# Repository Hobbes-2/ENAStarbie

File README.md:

ENA Themed Starbie

This project builds off of the basic Starbie tutorial with a focus on the game ENA: Dream BBQ. (In case you cant tell, ive been playing it). This is for week 1 of Hackclub Half Life. 

Its a fairly simple tamogatchi-esque PCB with two keys, a display, a MPU6050, an on-off switch, all running off of an ESP32.

This project is meant to serve as a useful tool to get back into PCB making, as Ive been slacking quite a bit when it comes to hardware. I hope that itll encourage me to keep doing the next weeks of Halflife, and Ill actually build good habits and gain knowledge about electrical circuts and PCBs. The original guide is this (https://github.com/SharKingStudios/Starbie/blob/main/Week%201%20Guide.md).

Customization
In addition to the custom silkscreens and borders that I added for this project, I also added some custom code in the firmware. The trail and sprite (Not finalized, i may draw a custom one soon) are both customized, though the art for the sprite is not mine (pulled it from the internet) and the actions the sprite takes is still the base code.

3D Renders 

Schematics

PCB Layout

BOM

| Part | Quantity | Unit Price (USD) | Vendor | Link |
|---|---:|---:|---|---|
| Cherry MX Key | 2 | $1.09 | AliExpress | [View Product](https://www.aliexpress.us/item/3256806626884956.html) |
| Display | 1 | $1.09 | AliExpress | [View Product](https://www.aliexpress.us/item/3256805954920554.html) |
| Resistor (10k) | 2 | $0.00 | AliExpress | [View Product](https://www.aliexpress.us/item/3256811723963477.html) |
| ESP32 | 1 | $2.65 | AliExpress | [View Product](https://www.aliexpress.us/item/3256809464129897.html) |
| DH11 | 1 | $1.57 | AliExpress | [View Product](https://www.aliexpress.us/item/3256807449697831.html) |
| Slide Switch | 1 | $2.39 | AliExpress | [View Product](https://www.aliexpress.us/item/3256808053858073.html) |
| PCB | 1 | $10.95 | JLCPCB | [Get Quote](https://cart.jlcpcb.com/quote/gerberviewThree/?qs=1fd10fe2350848d4ab924f033e7ffb15_1_0_1_0_0.html) |

(BOM formatted by AI)

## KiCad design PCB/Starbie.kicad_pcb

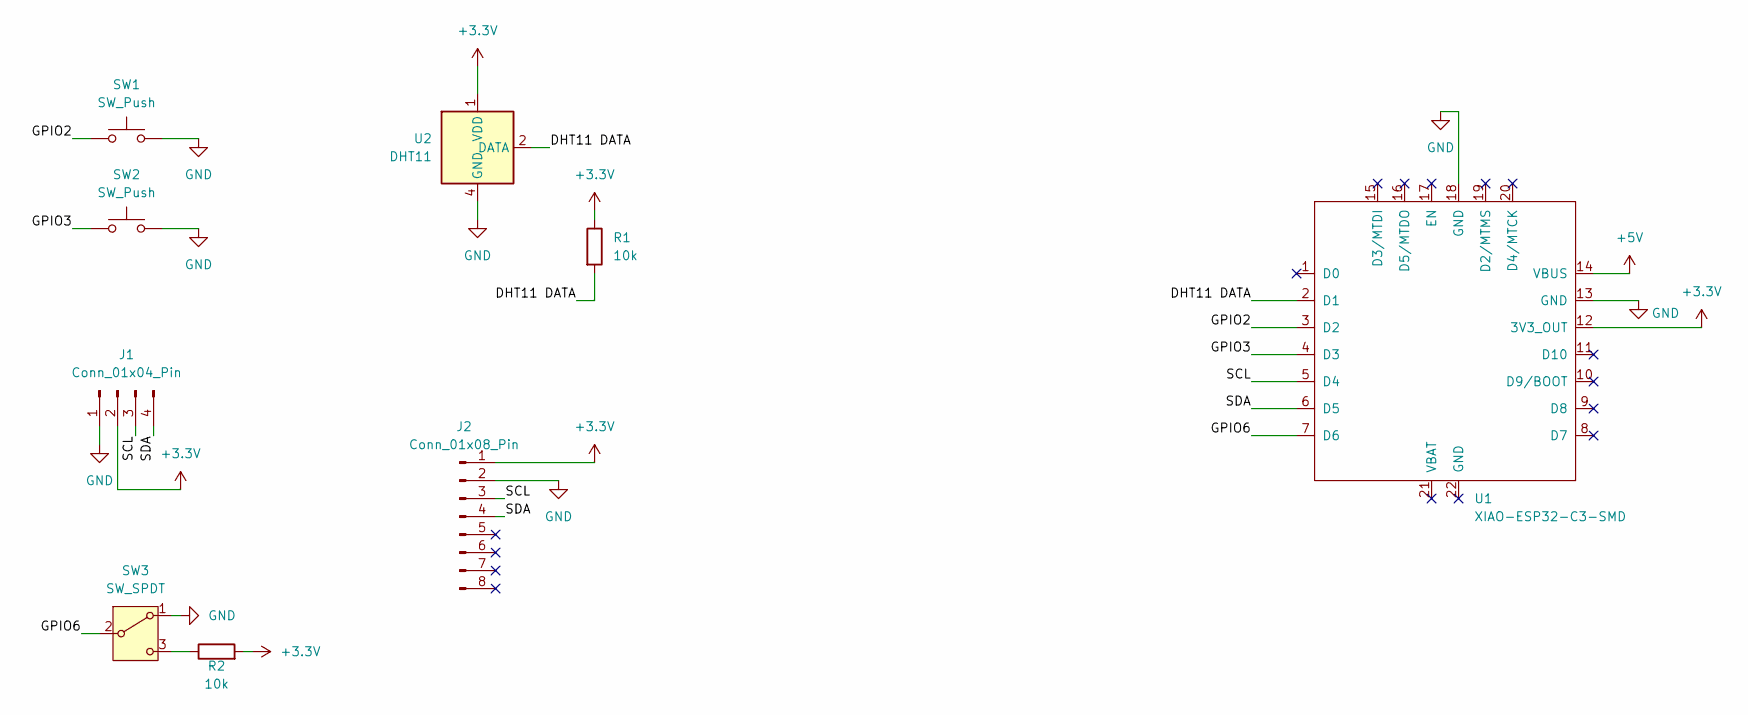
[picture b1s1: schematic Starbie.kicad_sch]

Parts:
J1: Conn_01x04_Pin; Display_128x64_096_I2C
J2: Conn_01x08_Pin; PinHeader_1x08_P2.54mm_Vertical
R1, R2: 10k; R_Axial_DIN0204_L3.6mm_D1.6mm_P7.62mm_Horizontal
SW1, SW2: SW_Push; SW_Cherry_MX_1.00u_PCB
SW3: SW_SPDT; PinHeader_1x03_P2.54mm_Horizontal
U1: XIAO-ESP32-C3-SMD
U2: DHT11; Aosong_DHT11_5.5x12.0_P2.54mm

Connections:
+3.3V: J1.2, J2.1, R1.1, R2.2, U1.12 (3V3_OUT), U2.1 (VDD)
+5V: U1.14 (VBUS)
/DHT11 DATA: R1.2, U1.2 (D1), U2.2 (DATA)
/GPIO2: SW1.1, U1.3 (D2)
/GPIO3: SW2.1, U1.4 (D3)
/GPIO6: SW3.2 (B), U1.7 (D6)
/SCL: J1.3, J2.3, U1.5 (D4)
/SDA: J1.4, J2.4, U1.6 (D5)
GND: J1.1, J2.2, SW1.2, SW2.2, SW3.1 (A), U1.13 (GND), U1.18 (GND), U2.4 (GND)
unnamed: R2.1, SW3.3 (C)

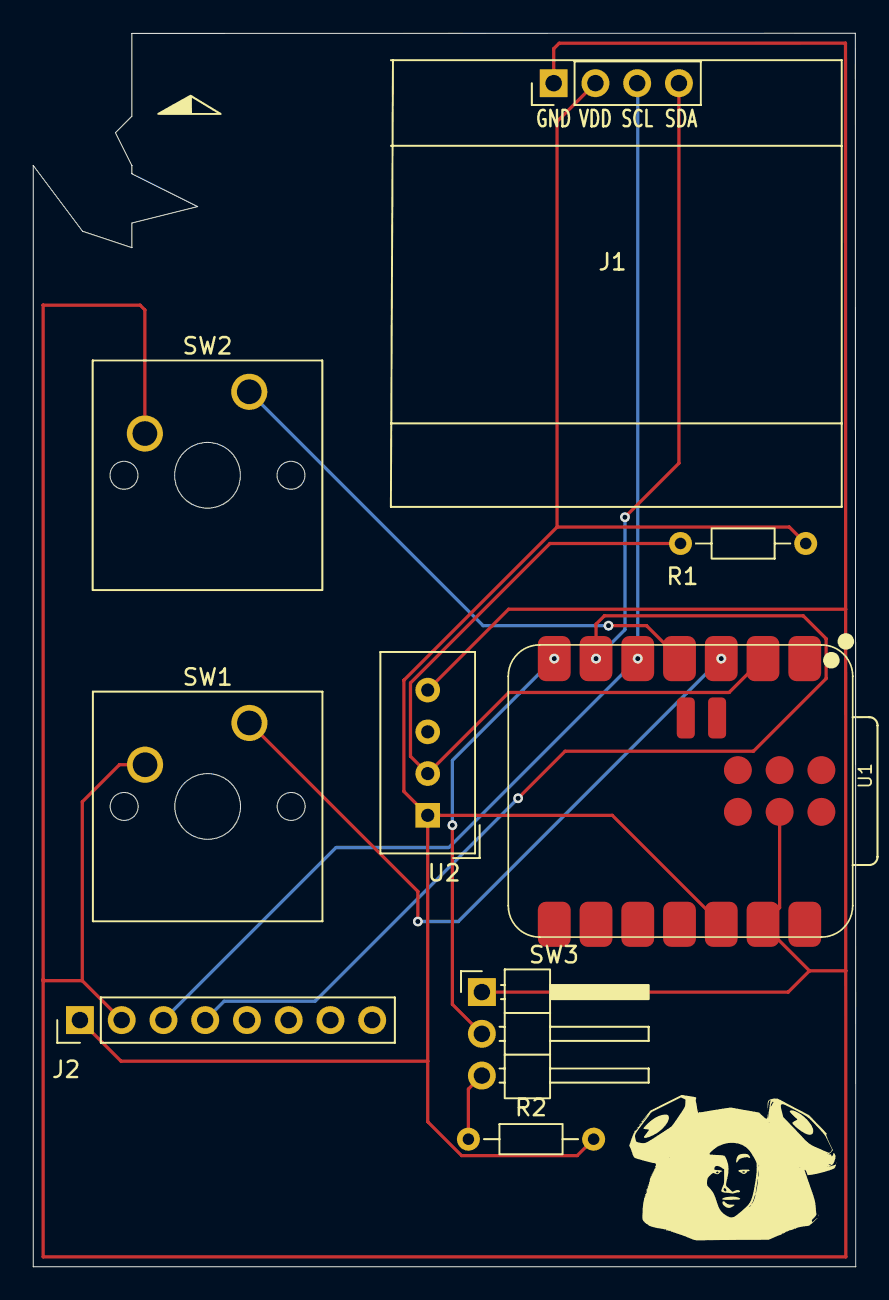
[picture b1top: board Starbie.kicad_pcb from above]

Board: 2 copper layers, 50.0 x 75.0 mm, 9 parts (0 on the bottom side), 9 nets.
